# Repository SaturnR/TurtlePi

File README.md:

TurtlePi
========

Programming and Electronics Learning Robotics kit, for students. 
 
TurtlePi is designed as a learning and research­experimenting robotics kit. 
It can be used for students from 12 year old to universities and colleges. 
kit is entirely modular, wide variety of sensors can be connected easily as a modules and 
actuators presented as a modules too. Robot contains two main board one is arduino 
compatible control board and another is raspberry pi computer, arduino control board is 
designed as shield for Raspberry Pi.  

Arduino board can be used as standalone control board, without Raspberry Pi computer and can 
perform low level tasks such as path planning, obstacle avoidance, line following, remote control. 
In addition with Raspberry Pi computer, robot gets much more complex functionality such as: 
object/face recognition, speech synthesis, Speech Recognition, dynamic programming and etc. 

robotics kit can be controlled and programmed wirelessly, 
In final design, robotics kit can be programmed with wide variety programming languages 
(python, javascript, c, c++, perl, c#) and visual languages like Google Blockly and Scratch.

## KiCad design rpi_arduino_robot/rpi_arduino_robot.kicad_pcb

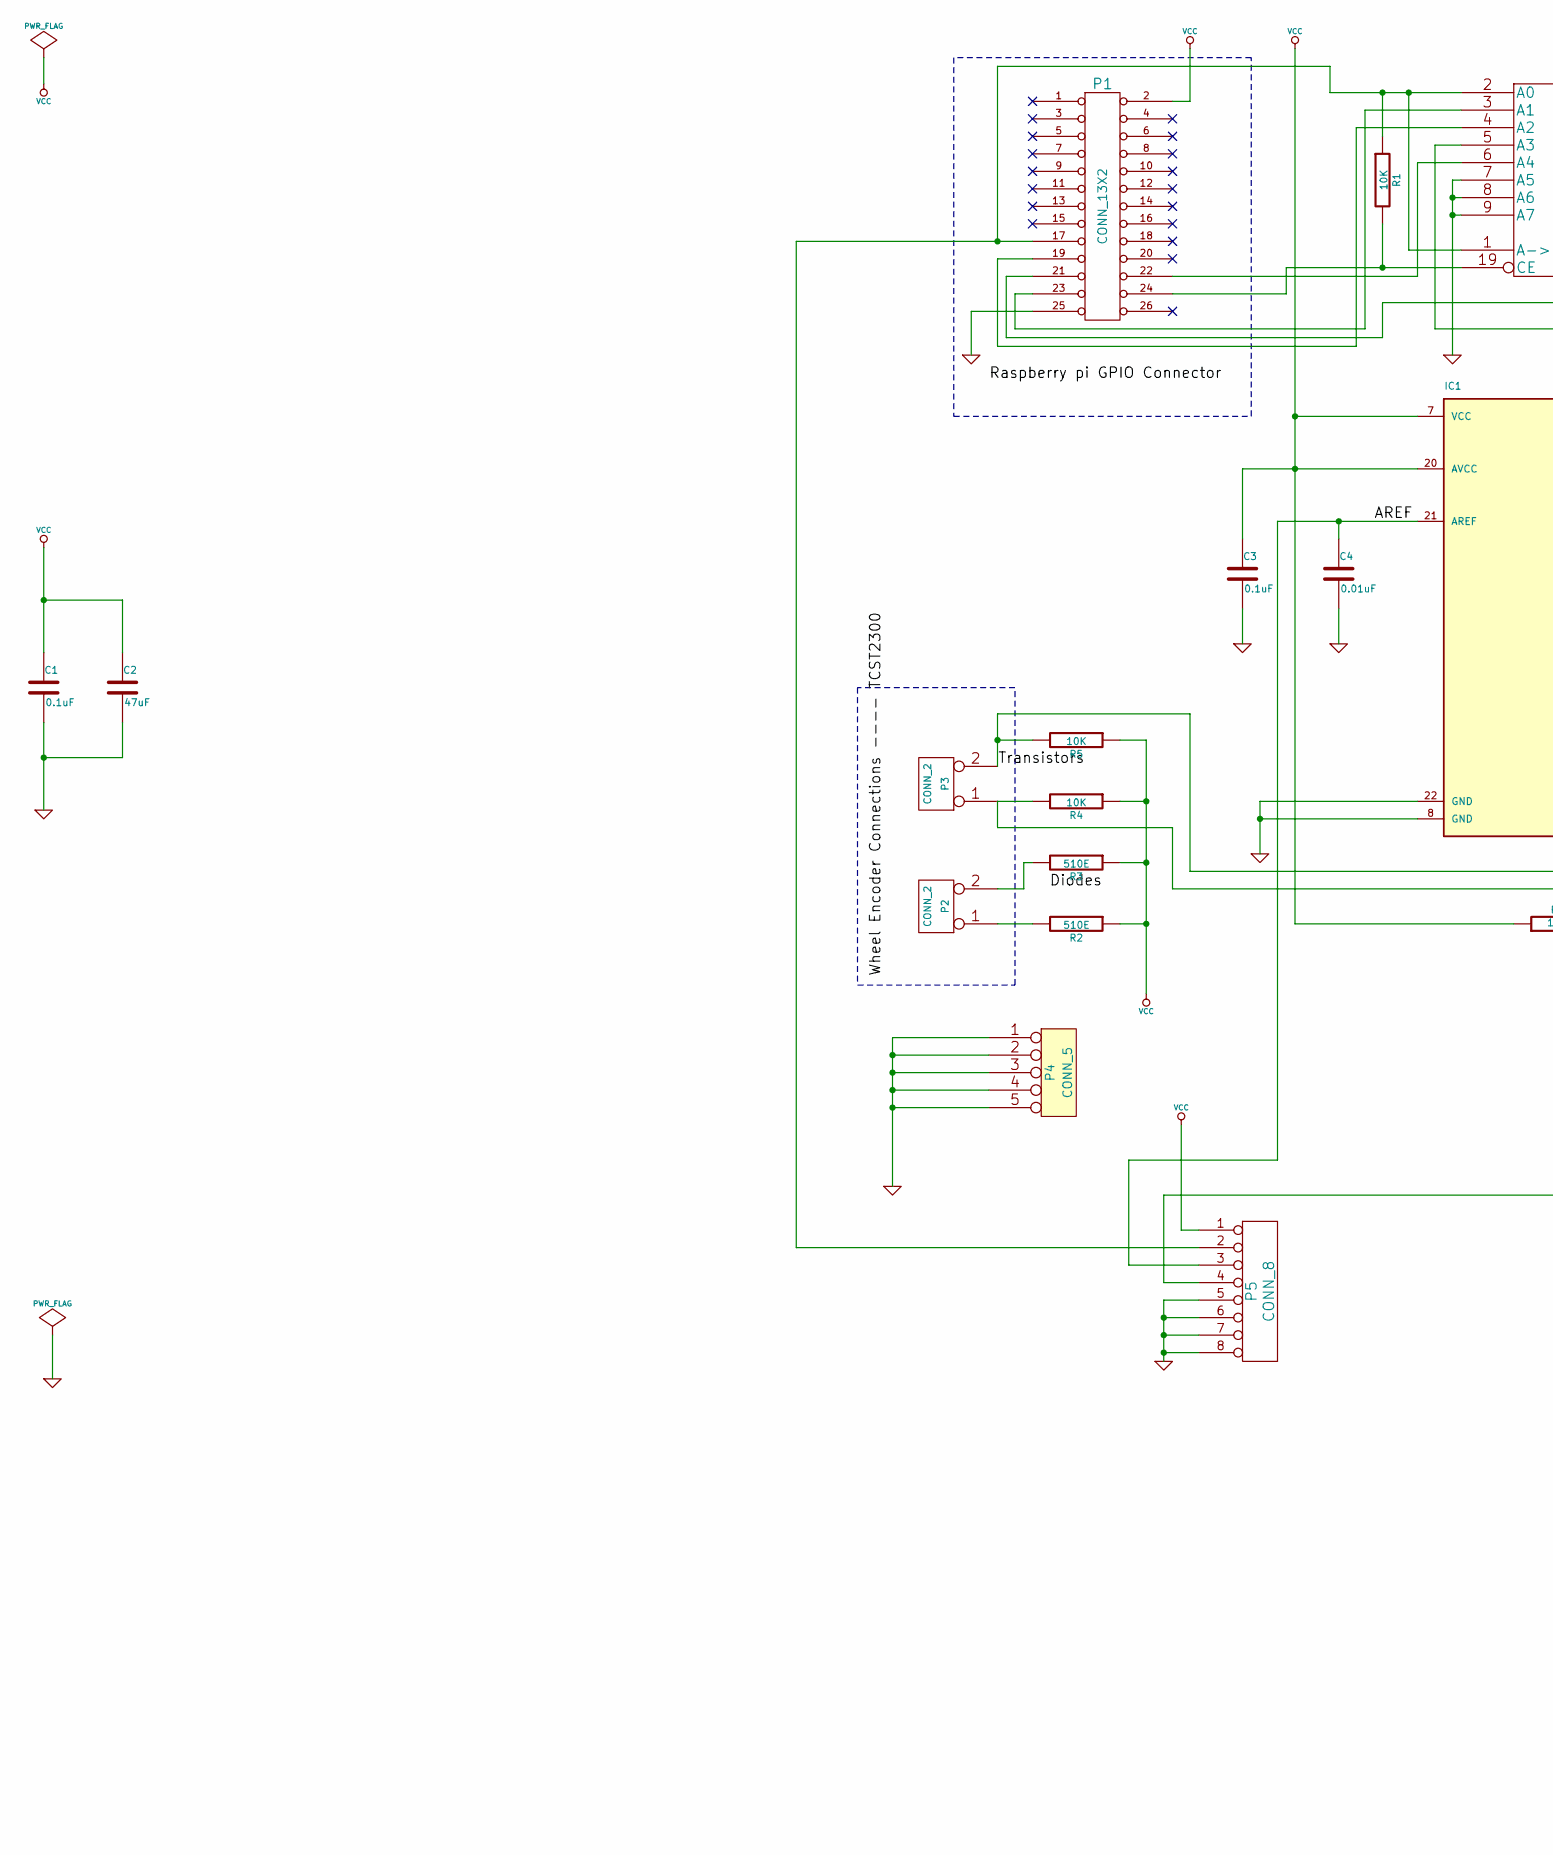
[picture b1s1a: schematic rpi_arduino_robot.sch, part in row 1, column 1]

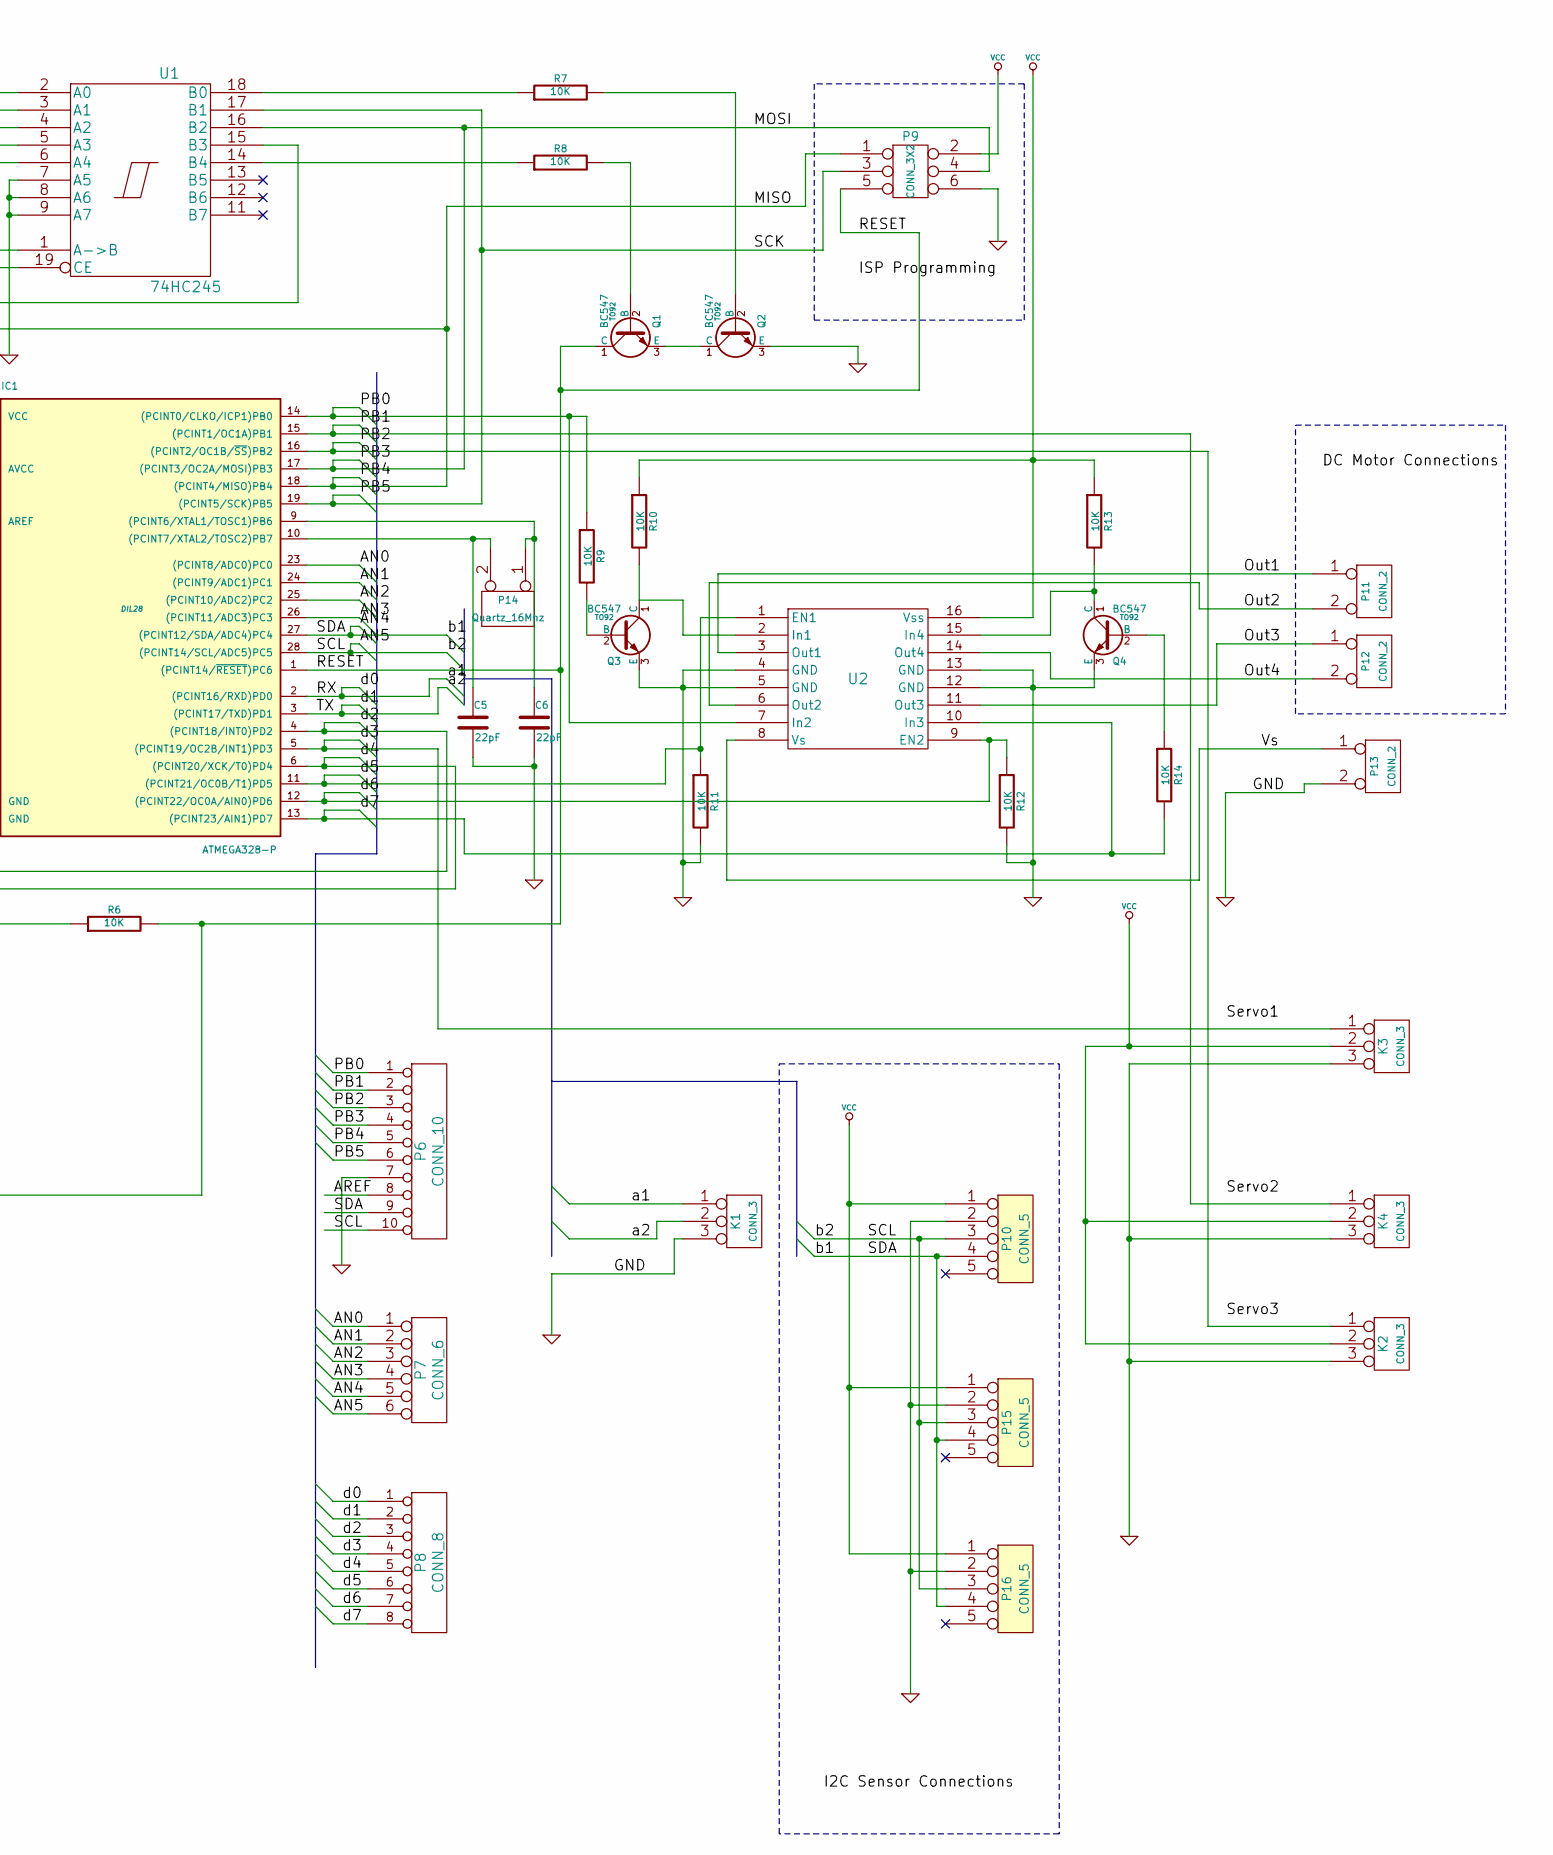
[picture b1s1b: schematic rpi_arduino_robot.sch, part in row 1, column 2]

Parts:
C1, C3: 0.1uF
C2: 47uF
C4: 0.01uF
C5, C6: 22pF
IC1: ATMEGA328-P; DIL28
K1, K2, K3, K4: CONN_3
P1: CONN_13X2
P2, P3, P11, P12, P13: CONN_2
P4, P10, P15, P16: CONN_5
P5, P8: CONN_8
P6: CONN_10
P7: CONN_6
P9: CONN_3X2
P14: Quartz_16Mhz
Q1, Q2, Q3, Q4: BC547; TO92
R1, R4, R5, R6, R7, R8, R9, R10, R11, R12, R13, R14: 10K
R2, R3: 510E
U1: 74HC245
U2: L293D

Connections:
/AN0: IC1.23 ((PCINT8/ADC0)PC0), P7.1
/AN1: IC1.24 ((PCINT9/ADC1)PC1), P7.2
/AN2: IC1.25 ((PCINT10/ADC2)PC2), P7.3
/AN3: IC1.26 ((PCINT11/ADC3)PC3), P7.4
/AN4: IC1.27 ((PCINT12/SDA/ADC4)PC4), P6.9, P7.5, P10.4, P15.4, P16.4
/AN5: IC1.28 ((PCINT14/SCL/ADC5)PC5), P6.10, P7.6, P10.3, P15.3, P16.3
/AREF: C4.1, IC1.21 (AREF), P5.3, P6.8
/MISO: IC1.18 ((PCINT4/MISO)PB4), P6.5, P9.1, U1.5 (A3)
/MOSI: IC1.17 ((PCINT3/OC2A/MOSI)PB3), P6.4, P9.4, U1.16 (B2)
/Out1: P11.1, U2.3 (Out1)
/Out2: P11.2 (PM), U2.6 (Out2)
/Out3: P12.1, U2.11 (Out3)
/Out4: P12.2 (PM), U2.14 (Out4)
/PB0: IC1.14 ((PCINT0/CLKO/ICP1)PB0), P6.1, R9.1, U2.7 (In2)
/PB1: IC1.15 ((PCINT1/OC1A)PB1), K4.1, P6.2
/PB2: IC1.16 ((PCINT2/OC1B/~SS~)PB2), K2.1, P6.3
/PB5: IC1.19 ((PCINT5/SCK)PB5), P6.6, P9.3, U1.17 (B1)
/RESET: IC1.1 ((PCINT14/~RESET~)PC6), P5.4, P9.5, Q1.1 (C), R6.2
/RX: IC1.2 ((PCINT16/RXD)PD0), K1.1, P8.1
/TX: IC1.3 ((PCINT17/TXD)PD1), K1.2 (PM), P8.2
/Vs: P13.1, U2.8 (Vs)
/d2: IC1.4 ((PCINT18/INT0)PD2), P3.2 (PM), P8.3, R5.2
/d3: IC1.5 ((PCINT19/OC2B/INT1)PD3), K3.1, P8.4
/d4: IC1.6 ((PCINT20/XCK/T0)PD4), P3.1, P8.5, R4.2
/d5: IC1.11 ((PCINT21/OC0B/T1)PD5), P8.6, R11.1, U2.1 (EN1)
/d6: IC1.12 ((PCINT22/OC0A/AIN0)PD6), P8.7, R12.1, U2.9 (EN2)
/d7: IC1.13 ((PCINT23/AIN1)PD7), P8.8, R14.2, U2.10 (In3)
GND: C1.2, C2.2, C3.2, C4.2, C5.2, C6.2, IC1.8 (GND), IC1.22 (GND), K1.3, K2.3, K3.3, K4.3, P1.25 (P24), P4.1, P4.2, P4.3, P4.4, P4.5, P5.5, P5.6, P5.7, P5.8, P6.7, P9.6, P10.2, P13.2 (PM), P15.2, P16.2, Q2.3 (E), Q3.3 (E), Q4.3 (E), R11.2, R12.2, U1.7 (A5), U1.8 (A6), U1.9 (A7), U1.10 (GND), U2.4 (GND), U2.5 (GND), U2.12 (GND), U2.13 (GND)
unnamed: P1.17, P5.2, R1.1, U1.1 (A->B), U1.2 (A0)
unnamed: P2.2 (PM), R3.2
unnamed: P2.1, R2.2
unnamed: P1.23, U1.3 (A1)
unnamed: P1.19, U1.4 (A2)
unnamed: P1.21, U1.15 (B3)
unnamed: P1.24 (P20), R1.2, U1.19 (CE)
unnamed: P1.22, U1.6 (A4)
unnamed: C5.1, IC1.10 ((PCINT7/XTAL2/TOSC2)PB7), P14.2 (PM)
unnamed: Q2.2 (B), R7.2
unnamed: Q1.2 (B), R8.2
unnamed: Q3.2 (B), R9.2
unnamed: R8.1, U1.14 (B4)
unnamed: R7.1, U1.18 (B0)
unnamed: Q3.1 (C), R10.2, U2.2 (In1)
unnamed: Q4.1 (C), R13.2, U2.15 (In4)
unnamed: Q1.3 (E), Q2.1 (C)
unnamed: Q4.2 (B), R14.1
unnamed: C6.1, IC1.9 ((PCINT6/XTAL1/TOSC1)PB6), P14.1
VCC: C1.1, C2.1, C3.1, IC1.7 (VCC), IC1.20 (AVCC), K2.2 (PM), K3.2 (PM), K4.2 (PM), P1.2, P5.1, P9.2, P10.1, P15.1, P16.1, R2.1, R3.1, R4.1, R5.1, R6.1, R10.1, R13.1, U1.20 (VCC), U2.16 (Vss)

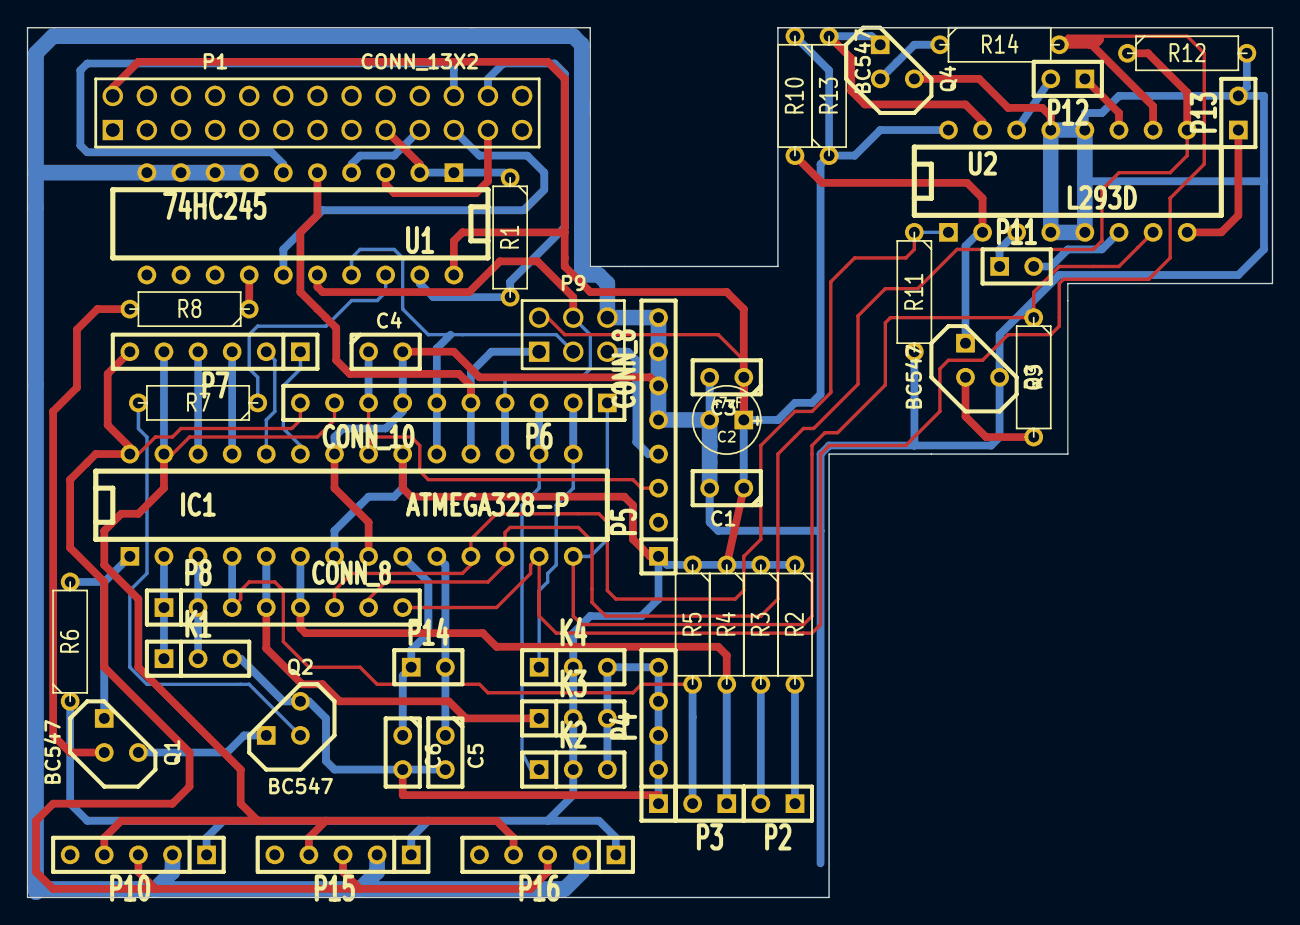
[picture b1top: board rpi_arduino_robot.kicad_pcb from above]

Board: 2 copper layers, 92.7 x 64.8 mm, 47 parts (0 on the bottom side), 48 nets.

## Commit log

2014-09-22 project commit 23 september 2014
2014-09-22 commit arduPi files
